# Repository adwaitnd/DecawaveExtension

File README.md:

# DecawaveExtension
Extension Board for Decawave Module

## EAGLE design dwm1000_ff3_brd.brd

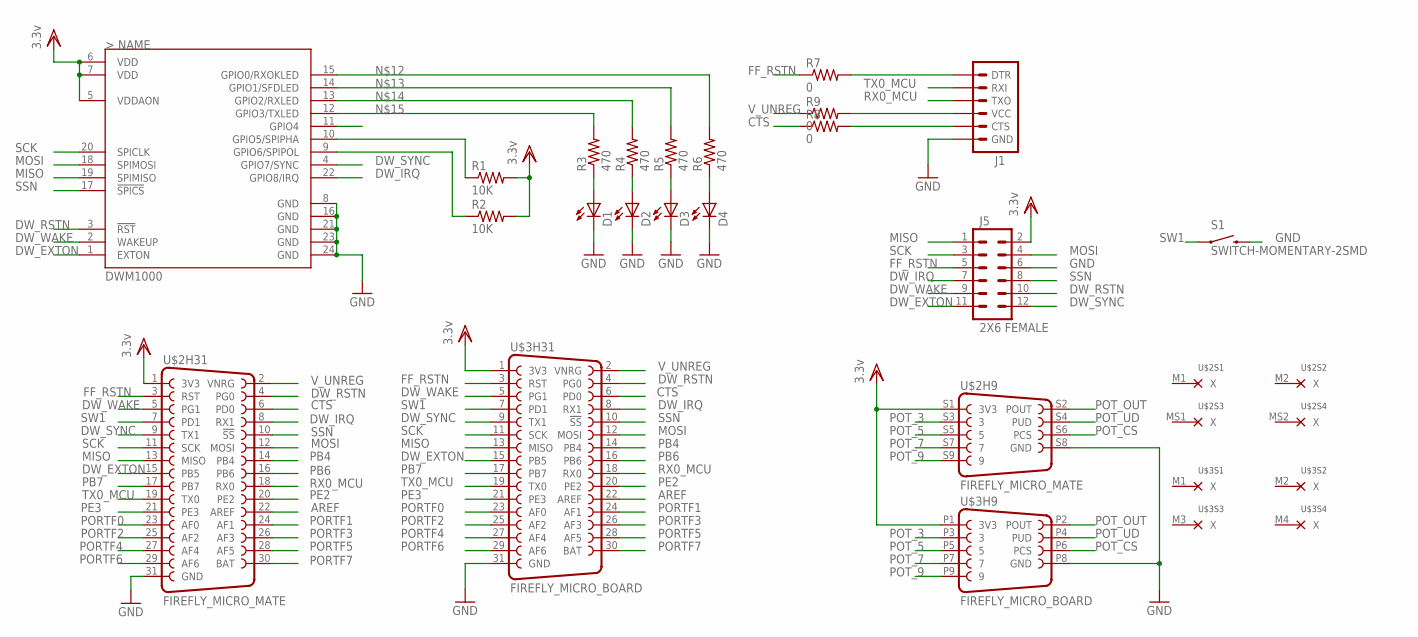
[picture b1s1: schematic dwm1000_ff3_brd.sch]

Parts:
D1, D2, D3, D4: LEDCHIP-LED0603; CHIP-LED0603
J1: ARDUINO_SERIAL_PROGRAMPTH; 1X06
J5: 2X6 FEMALE; 2X6
R1, R2: 10K; R0603
R3, R4, R5, R6: 470; R0603
R7, R8, R9: 0; R0603
S1: SWITCH-MOMENTARY-2SMD; TACTILE-SWITCH-SMD
U$1: DWM1000
U$2: FIREFLY_MICRO_MATE
U$3: FIREFLY_MICRO_BOARD

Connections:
AREF: U$2.22 (AREF), U$3.22 (AREF)
CTS: R8.1, U$2.6 (PD0), U$3.6 (PD0)
DW_EXTON: J5.11, U$1.1 (EXTON), U$2.15 (PB5), U$3.15 (PB5)
DW_IRQ: J5.7, U$1.22 (GPIO8/IRQ), U$2.8 (RX1), U$3.8 (RX1)
DW_RSTN: J5.10, U$1.3 (!RST), U$2.4 (PG0), U$3.4 (PG0)
DW_SYNC: J5.12, U$1.4 (GPIO7/SYNC), U$2.9 (TX1), U$3.9 (TX1)
DW_WAKE: J5.9, U$1.2 (WAKEUP), U$2.5 (PG1), U$3.5 (PG1)
FF_RSTN: J5.5, R7.1, U$2.3 (RST), U$3.3 (RST)
GND: D1.C, D2.C, D3.C, D4.C, J1.6 (GND), J5.6, S1.3 (2), U$1.8 (GND), U$1.16 (GND), U$1.21 (GND), U$1.23 (GND), U$1.24 (GND), U$2.31 (GND), U$2.S8 (GND), U$3.31 (GND), U$3.P8 (GND)
MISO: J5.1, U$1.19 (SPIMISO), U$2.13 (MISO), U$3.13 (MISO)
MOSI: J5.4, U$1.18 (SPIMOSI), U$2.12 (MOSI), U$3.12 (MOSI)
unnamed: D1.A, R3.1
unnamed: R1.1, U$1.10 (GPIO5/SPIPHA)
unnamed: D2.A, R4.1
unnamed: D3.A, R5.1
unnamed: D4.A, R6.1
unnamed: J1.4 (VCC), R9.2
unnamed: R2.1, U$1.9 (GPIO6/SPIPOL)
unnamed: R6.2, U$1.15 (GPIO0/RXOKLED)
unnamed: R5.2, U$1.14 (GPIO1/SFDLED)
unnamed: R4.2, U$1.13 (GPIO2/RXLED)
unnamed: R3.2, U$1.12 (GPIO3/TXLED)
unnamed: J1.1 (DTR), R7.2
unnamed: J1.5 (CTS), R8.2
PB4: U$2.14 (PB4), U$3.14 (PB4)
PB6: U$2.16 (PB6), U$3.16 (PB6)
PB7: U$2.17 (PB7), U$3.17 (PB7)
PE2: U$2.20 (PE2), U$3.20 (PE2)
PE3: U$2.21 (PE3), U$3.21 (PE3)
PORTF0: U$2.23 (AF0), U$3.23 (AF0)
PORTF1: U$2.24 (AF1), U$3.24 (AF1)
PORTF2: U$2.25 (AF2), U$3.25 (AF2)
PORTF3: U$2.26 (AF3), U$3.26 (AF3)
PORTF4: U$2.27 (AF4), U$3.27 (AF4)
PORTF5: U$2.28 (AF5), U$3.28 (AF5)
PORTF6: U$2.29 (AF6), U$3.29 (AF6)
PORTF7: U$2.30 (BAT), U$3.30 (BAT)
POT_3: U$2.S3 (3), U$3.P3 (3)
POT_5: U$2.S5 (5), U$3.P5 (5)
POT_7: U$2.S7 (7), U$3.P7 (7)
POT_9: U$2.S9 (9), U$3.P9 (9)
POT_CS: U$2.S6 (PCS), U$3.P6 (PCS)
POT_OUT: U$2.S2 (POUT), U$3.P2 (POUT)
POT_UD: U$2.S4 (PUD), U$3.P4 (PUD)
RX0_MCU: J1.3 (TXO), U$2.18 (RX0), U$3.18 (RX0)
SCK: J5.3, U$1.20 (SPICLK), U$2.11 (SCK), U$3.11 (SCK)
SSN: J5.8, U$1.17 (!SPICS), U$2.10 (!SS), U$3.10 (!SS)
SW1: S1.1, U$2.7 (PD1), U$3.7 (PD1)
TX0_MCU: J1.2 (RXI), U$2.19 (TX0), U$3.19 (TX0)
VDD: J5.2, R1.2, R2.2, U$1.5 (VDDAON), U$1.6 (VDD), U$1.7 (VDD), U$2.1 (3V3), U$2.S1 (3V3), U$3.1 (3V3), U$3.P1 (3V3)
V_UNREG: R9.1, U$2.2 (VNRG), U$3.2 (VNRG)

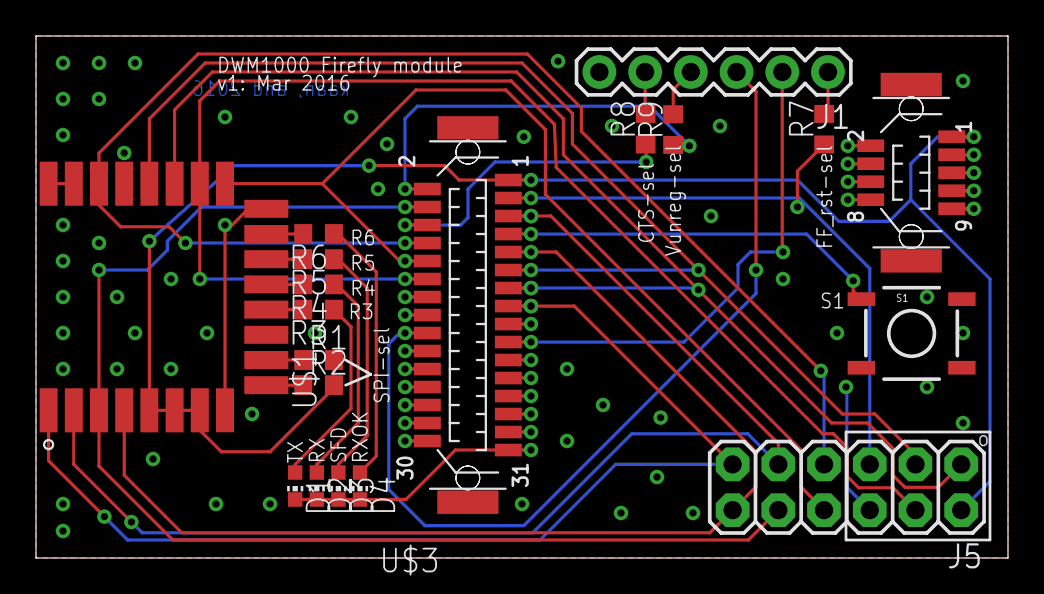
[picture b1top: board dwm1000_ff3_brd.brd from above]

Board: 2 copper layers, 54.0 x 29.0 mm, 19 parts (1 on the bottom side), 51 nets.

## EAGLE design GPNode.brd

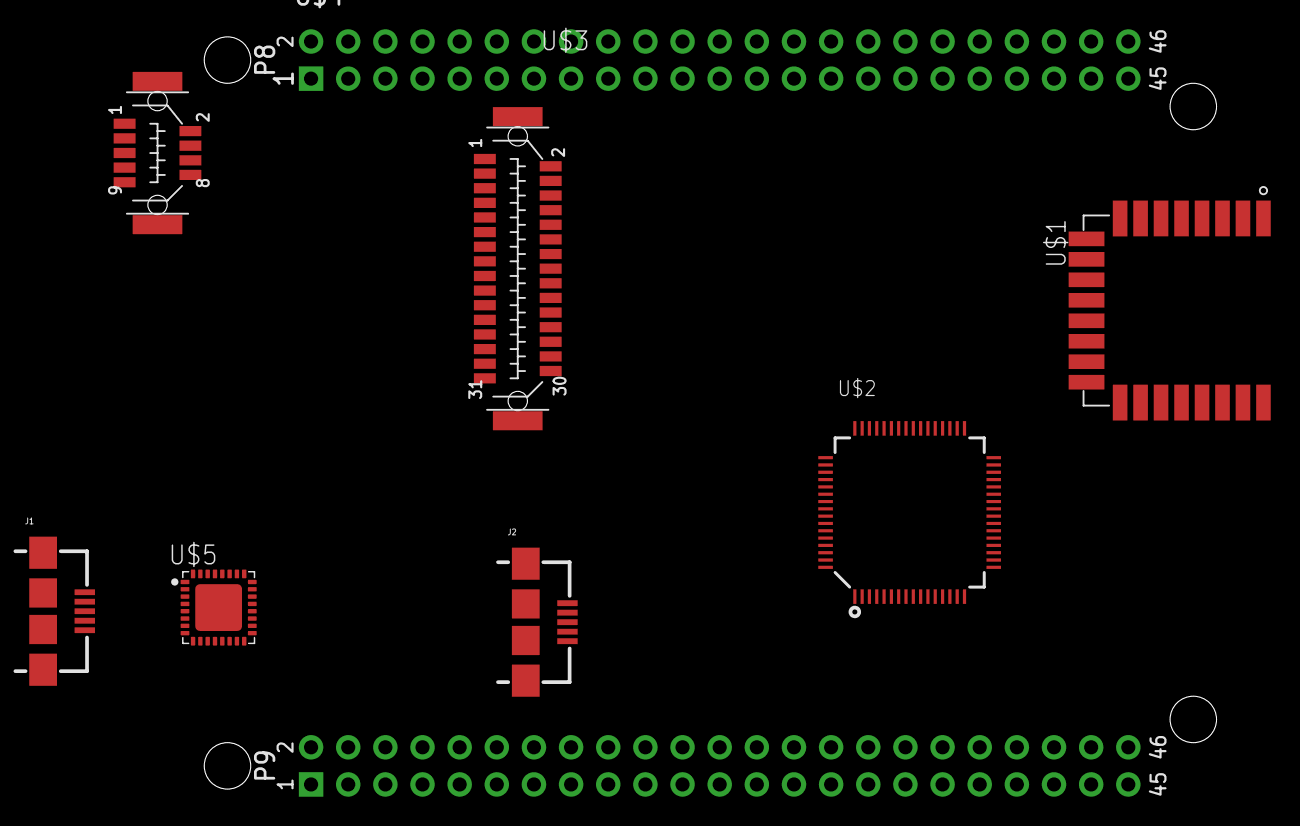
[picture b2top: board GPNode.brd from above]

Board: 2 copper layers, 12 parts (0 on the bottom side), 11 nets, no tracks yet.

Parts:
FRAME1, FRAME2, FRAME3, FRAME4, FRAME5: FRAME-LETTERNO_PACKAGE; DUMMY
J1, J2: USB-AB-MICRO-SMD
U$1: DWM1000
U$2: MK22FNXXXVLHXX; TQFP64
U$3: FIREFLY_MICRO
U$4: BEAGLE_BONE_BLACK_CAPE_DIP; BEAGLE_BONE_BLACK_CAPE
U$5: MK20DXXXXVFMX; QFN32

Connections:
3V3: U$3.1, U$3.S1
DGND: U$4.P8.1, U$4.P8.2, U$4.P9.1, U$4.P9.2, U$4.P9.43, U$4.P9.44, U$4.P9.45, U$4.P9.46
GND: U$1.8, U$1.16, U$1.21, U$1.23, U$1.24, U$3.31, U$3.S8
VBAT: U$2.21, U$5.11
VDD: U$1.6, U$1.7, U$2.3, U$2.30, U$2.48, U$5.1
VDDA: U$2.13, U$5.7
VDD_3V3: U$4.P9.3, U$4.P9.4
VDD_5V: U$4.P9.5, U$4.P9.6
VREGIN: U$2.8, U$5.6
VSS: U$2.4, U$2.31, U$2.47, U$5.2
VSSA: U$2.16, U$5.8

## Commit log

2016-02-21 added gitignore. Project initialized in the appropriate location but not added
2016-03-18 WIP files for FF & K22 DWM1000 module
2016-03-19 added firefly DWM1000 module
2016-03-20 width change to 7mil, minor fix to gnd via
2016-03-20 added gerber files

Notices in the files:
parts and their libraries:
SparkFun-Aesthetics: Licensing: Creative Commons ShareAlike 4.0 International - https://creativecommons.org/licenses/by-sa/4.0
